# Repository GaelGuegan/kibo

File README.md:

# KIBO project

It consists of a panel of 5x5 addressable leds that could be configured through bluetooth.

It is powered by a 3.7V single cell lipo battery, that could be recharged through usb-c.

Leds are controlled by a single GPIO pin with signal passing through a 5V level shifter.

## Software

- Zephyr OS
- Android Studio

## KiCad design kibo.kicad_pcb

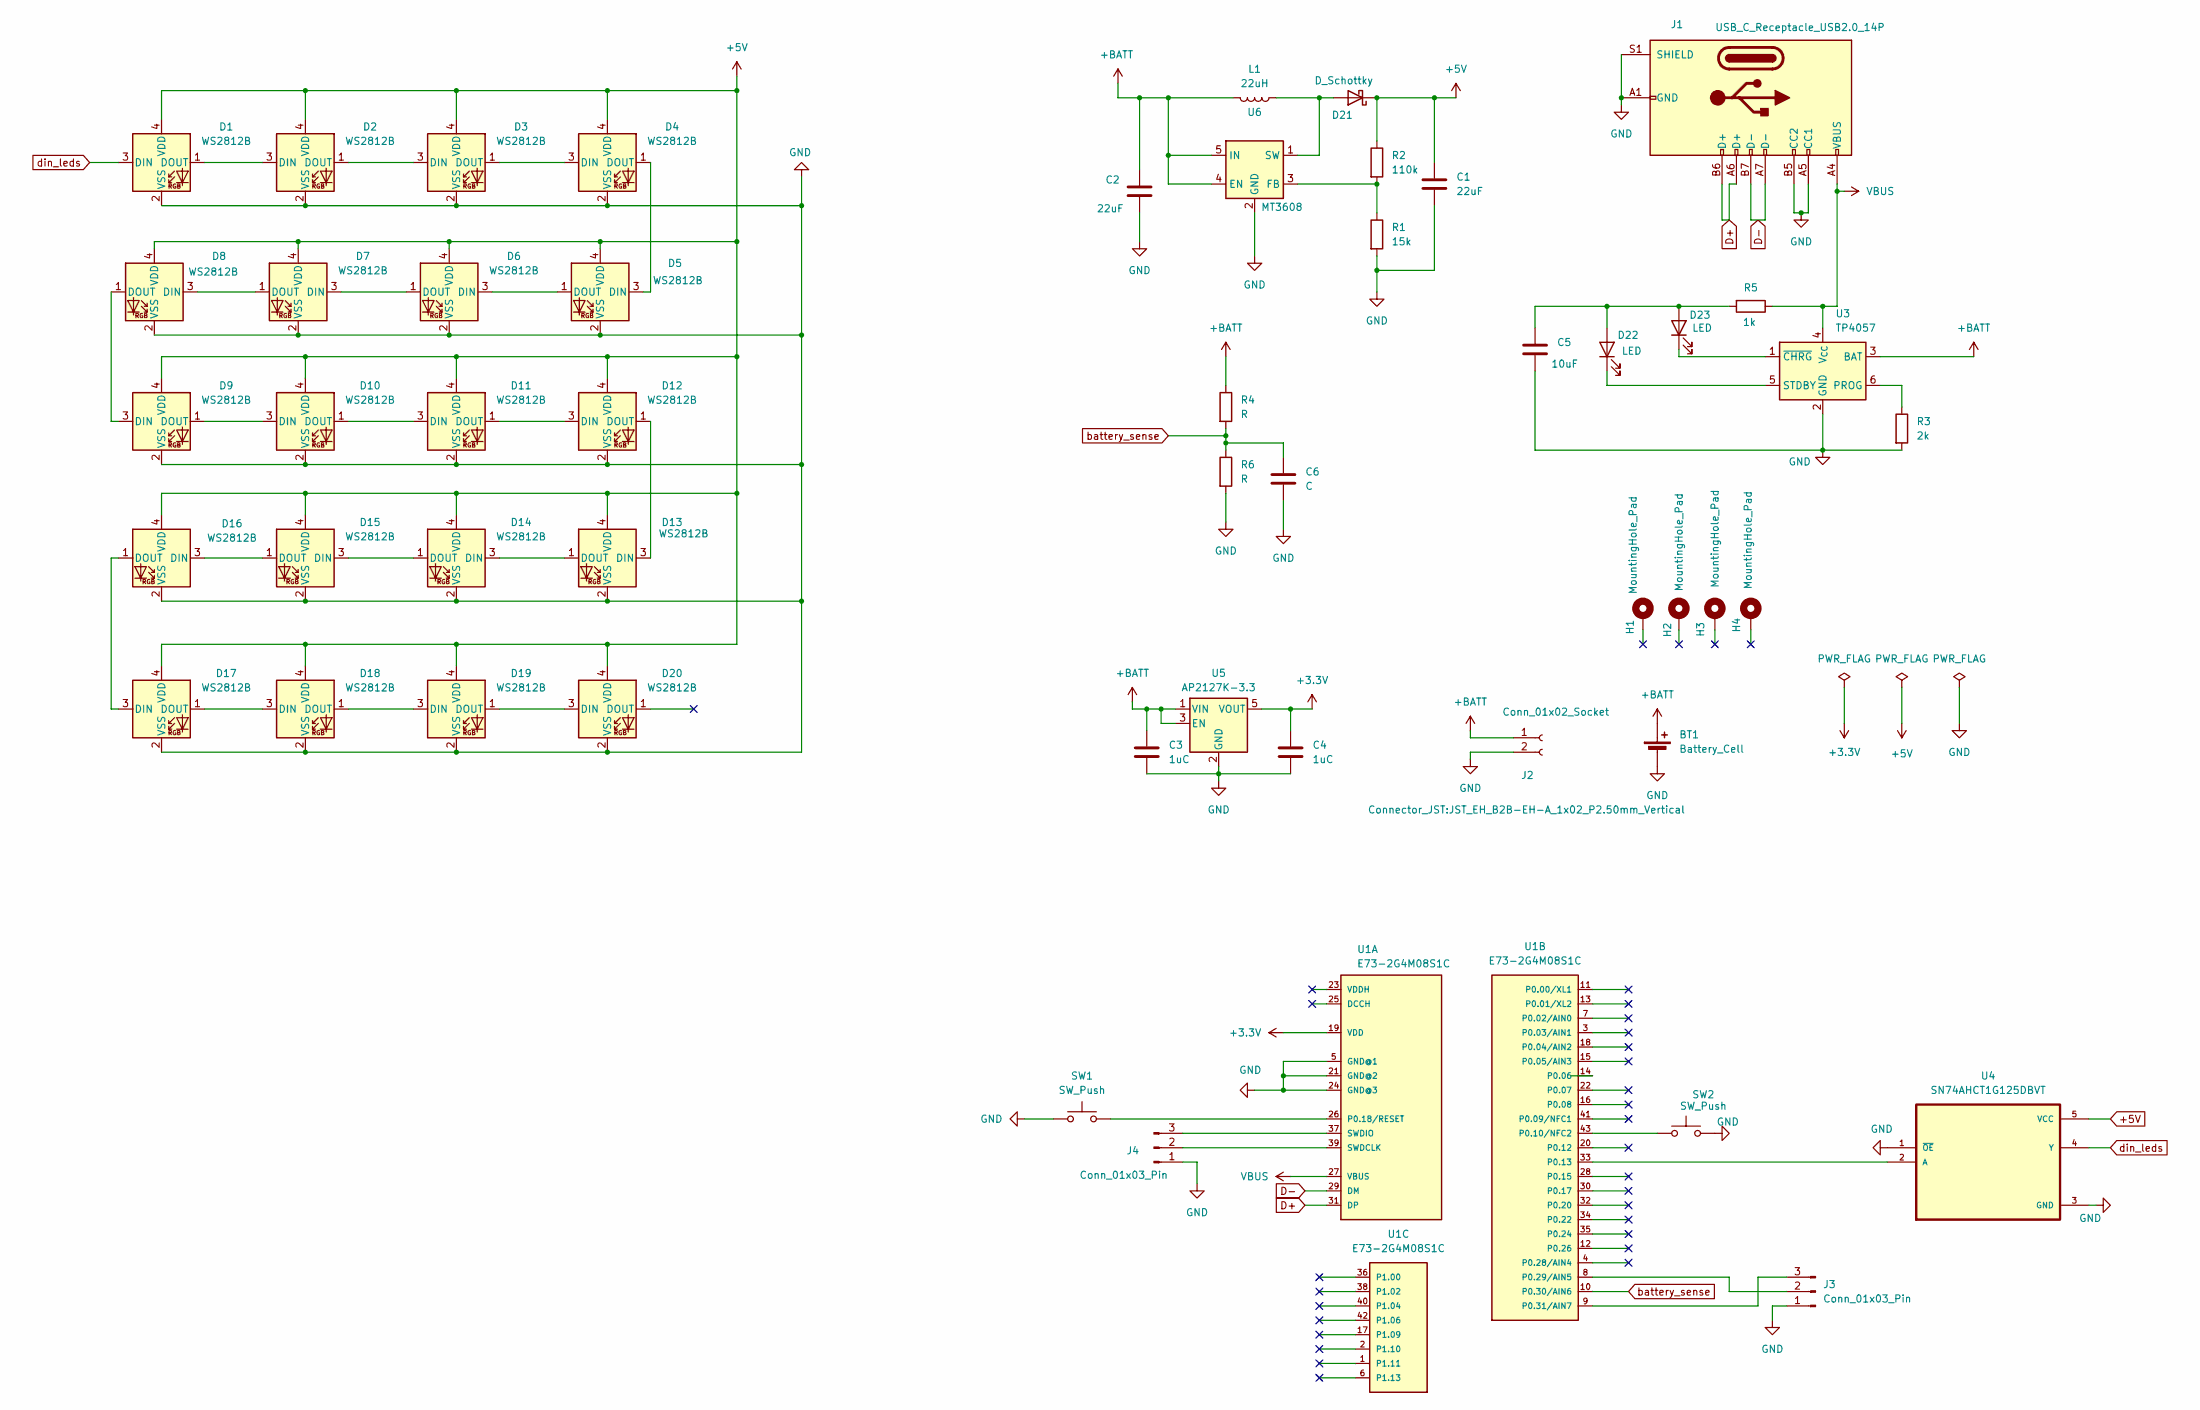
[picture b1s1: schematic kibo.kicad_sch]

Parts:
BT1: Battery_Cell
C1, C2: 22uF; C_0805_2012Metric
C3, C4: 1uC; C_0805_2012Metric
C5: 10uF; C_0805_2012Metric
C6: C; C_0805_2012Metric
D1, D2, D3, D4, D5, D6, D7, D8, D9, D10, D11, D12, D13, D14, D15, D16, D17, D18, D19, D20: WS2812B; LED_WS2812B-2020_PLCC4_2.0x2.0mm
D21: D_Schottky
D22, D23: LED
H1: MountingHole_Pad; MountingHole_2.5mm_Pad
H2, H3, H4: MountingHole_Pad; MountingHole_2.2mm_M2_Pad
J1: USB_C_Receptacle_USB2.0_14P; USB_C_Receptacle_Palconn_UTC16-G
J2: Conn_01x02_Socket; JST_EH_B2B-EH-A_1x02_P2.50mm_Vertical
J3, J4: Conn_01x03_Pin; PinHeader_1x03_P2.00mm_Vertical
L1: 22uH; L_0805_2012Metric
R1: 15k; R_0805_2012Metric
R2: 110k; R_0805_2012Metric
R3: 2k; R_0805_2012Metric
R4, R6: R; R_0805_2012Metric
R5: 1k; R_0805_2012Metric
SW1, SW2: SW_Push; SW_SPST_EVQP2_ShortPushTravel_H2.5mm
U1: E73-2G4M08S1C
U3: TP4057; TSOT-23-6
U4: SN74AHCT1G125DBVT; SOT95P280X145-5N
U5: AP2127K-3.3; SOT-23-5
U6: MT3608; SOT-23-6

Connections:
+3.3V: C4.1, U1.19 (VDD), U5.5 (VOUT)
+5V: C1.1, D1.4 (VDD), D2.4 (VDD), D3.4 (VDD), D4.4 (VDD), D5.4 (VDD), D6.4 (VDD), D7.4 (VDD), D8.4 (VDD), D9.4 (VDD), D10.4 (VDD), D11.4 (VDD), D12.4 (VDD), D13.4 (VDD), D14.4 (VDD), D15.4 (VDD), D16.4 (VDD), D17.4 (VDD), D18.4 (VDD), D19.4 (VDD), D20.4 (VDD), D21.1 (K), R2.1, U4.5 (VCC)
+BATT: BT1.1 (+), C2.1, C3.1, J2.1, L1.2, R4.1, U3.3 (BAT), U5.1 (VIN), U5.3 (EN), U6.4 (EN), U6.5 (IN)
D+: J1.A6 (D+), J1.B6 (D+), U1.31 (DP)
D-: J1.A7 (D-), J1.B7 (D-), U1.29 (DM)
GND: BT1.2 (-), C1.2, C2.2, C3.2, C4.2, C5.2, C6.2, D1.2 (VSS), D2.2 (VSS), D3.2 (VSS), D4.2 (VSS), D5.2 (VSS), D6.2 (VSS), D7.2 (VSS), D8.2 (VSS), D9.2 (VSS), D10.2 (VSS), D11.2 (VSS), D12.2 (VSS), D13.2 (VSS), D14.2 (VSS), D15.2 (VSS), D16.2 (VSS), D17.2 (VSS), D18.2 (VSS), D19.2 (VSS), D20.2 (VSS), J1.A1 (GND), J1.A5 (CC1), J1.A12 (GND), J1.B1 (GND), J1.B5 (CC2), J1.B12 (GND), J1.S1 (SHIELD), J2.2, J3.1, J4.1, R1.2, R3.2, R6.2, SW1.1, SW2.2, U1.5 (GND@1), U1.21 (GND@2), U1.24 (GND@3), U3.2 (GND), U4.1 (~OE), U4.3 (GND), U5.2 (GND), U6.2 (GND)
unnamed: D1.1 (DOUT), D2.3 (DIN)
unnamed: D2.1 (DOUT), D3.3 (DIN)
unnamed: D3.1 (DOUT), D4.3 (DIN)
unnamed: D4.1 (DOUT), D5.3 (DIN)
unnamed: D5.1 (DOUT), D6.3 (DIN)
unnamed: D6.1 (DOUT), D7.3 (DIN)
unnamed: D7.1 (DOUT), D8.3 (DIN)
unnamed: D8.1 (DOUT), D9.3 (DIN)
unnamed: D9.1 (DOUT), D10.3 (DIN)
unnamed: D10.1 (DOUT), D11.3 (DIN)
unnamed: D11.1 (DOUT), D12.3 (DIN)
unnamed: D12.1 (DOUT), D13.3 (DIN)
unnamed: D13.1 (DOUT), D14.3 (DIN)
unnamed: D14.1 (DOUT), D15.3 (DIN)
unnamed: D15.1 (DOUT), D16.3 (DIN)
unnamed: D16.1 (DOUT), D17.3 (DIN)
unnamed: D17.1 (DOUT), D18.3 (DIN)
unnamed: D18.1 (DOUT), D19.3 (DIN)
unnamed: D19.1 (DOUT), D20.3 (DIN)
unnamed: D21.2 (A), L1.1, U6.1 (SW)
unnamed: C5.1, D22.2 (A), D23.2 (A), R5.2
unnamed: D22.1 (K), U3.5 (STDBY)
unnamed: D23.1 (K), U3.1 (~CHRG)
unnamed: J3.2, U1.8 (P0.29/AIN5)
unnamed: J3.3, U1.9 (P0.31/AIN7)
unnamed: J4.2, U1.39 (SWDCLK)
unnamed: J4.3, U1.37 (SWDIO)
unnamed: SW1.2, U1.26 (P0.18/RESET)
unnamed: SW2.1, U1.43 (P0.10/NFC2)
unnamed: U1.33 (P0.13), U4.2 (A)
unnamed: R3.1, U3.6 (PROG)
unnamed: R1.1, R2.2, U6.3 (FB)
VBUS: J1.A4 (VBUS), J1.A9 (VBUS), J1.B4 (VBUS), J1.B9 (VBUS), R5.1, U1.27 (VBUS), U3.4 (V_{CC})
battery_sense: C6.1, R4.2, R6.1, U1.10 (P0.30/AIN6)
din_leds: D1.3 (DIN), U4.4 (Y)

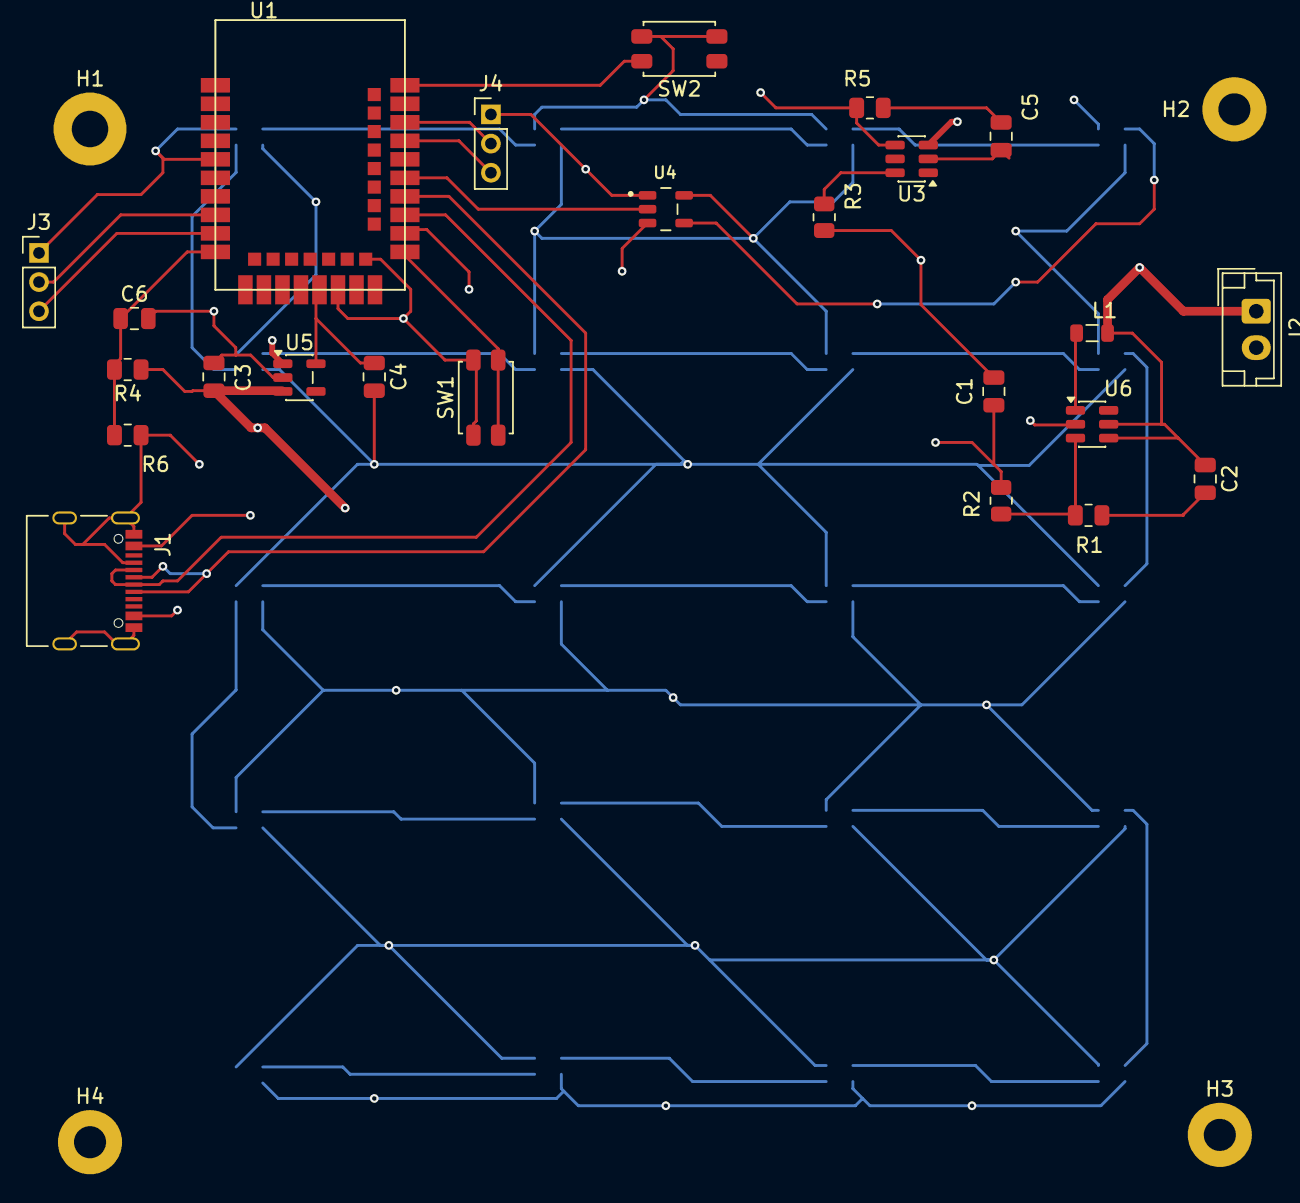
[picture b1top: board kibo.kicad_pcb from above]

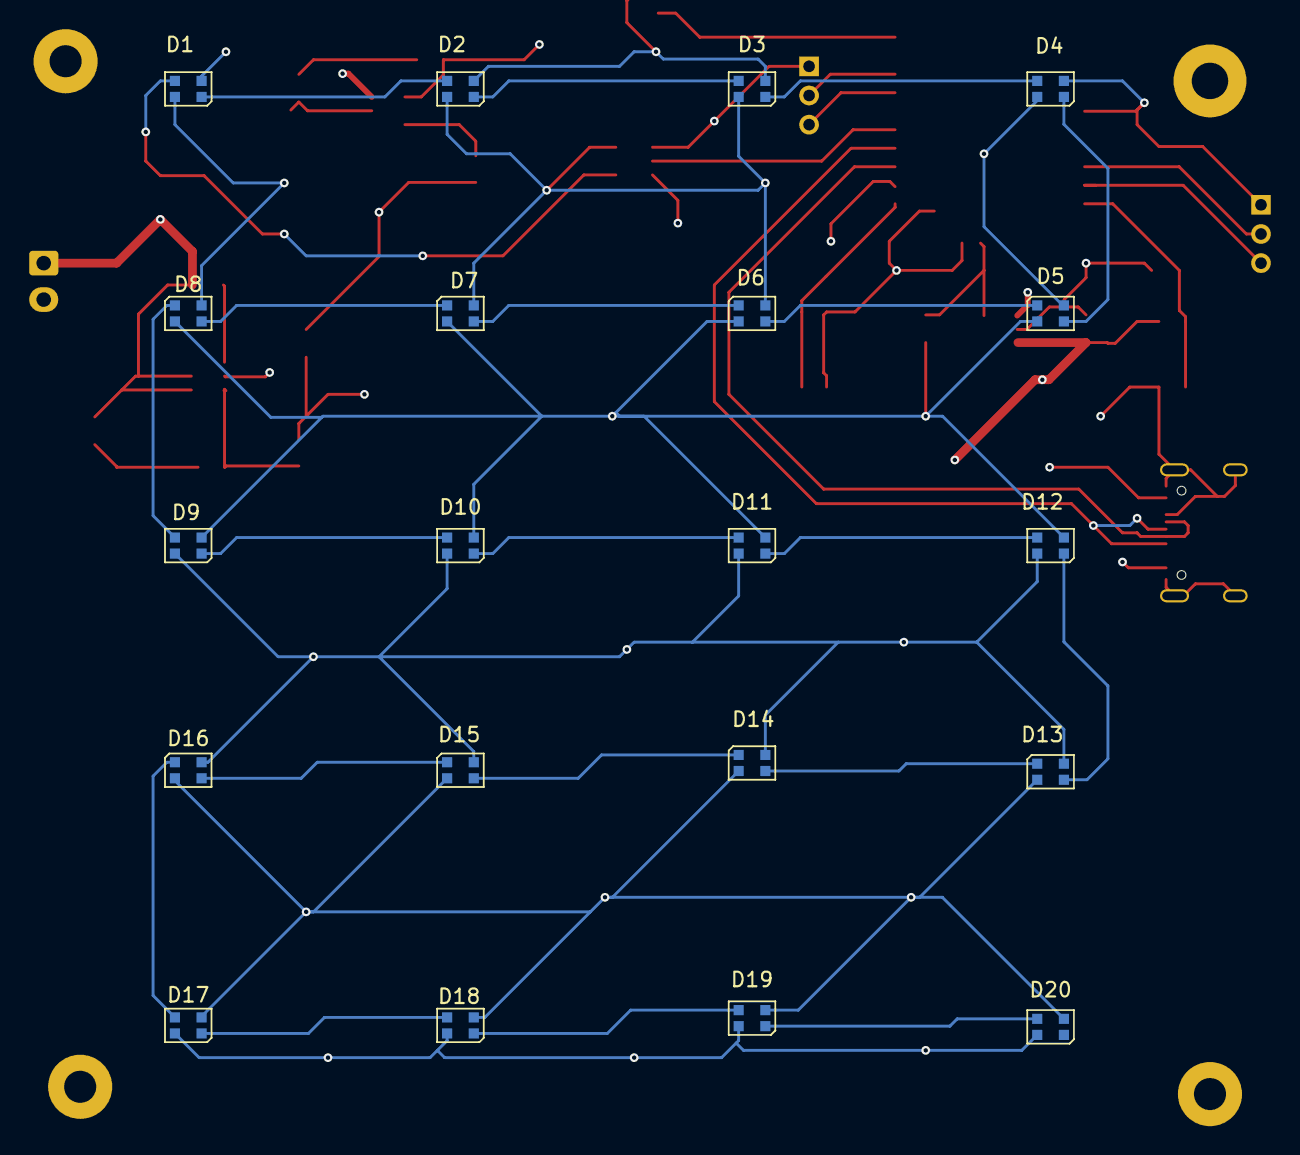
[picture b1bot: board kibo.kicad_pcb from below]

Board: 4 copper layers, 48 parts (20 on the bottom side), 39 nets.

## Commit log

2025-10-22 Update schematics
2025-12-02 Remove datasheet and add BOM
2025-12-05 fisrt version minimal
2025-12-09 update schematic
